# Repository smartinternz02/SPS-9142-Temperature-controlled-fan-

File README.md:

# SPS-9142-Temperature-controlled-fan-
Temperature controlled fan 

Link gor project demonstration video.
https://drive.google.com/file/d/1OC6MNtlAbGEZ7j19aoUIXOwhLdMn7zE-/view?usp=drivesdk

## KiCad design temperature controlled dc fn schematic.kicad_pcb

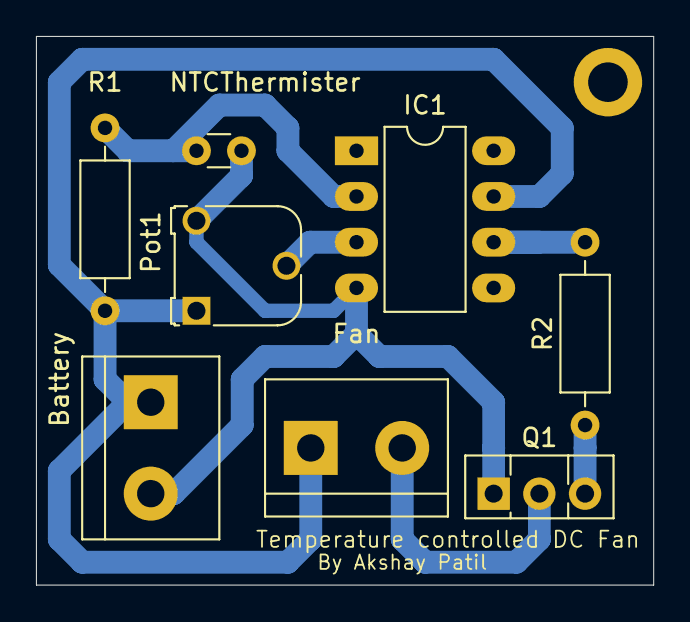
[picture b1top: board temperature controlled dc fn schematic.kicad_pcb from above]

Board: 2 copper layers, 34.3 x 30.5 mm, 8 parts (0 on the bottom side), 7 nets.

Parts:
Battery: 12 volts; TerminalBlock_bornier-2_P5.08mm
Fan: Fan; TerminalBlock_bornier-2_P5.08mm
IC1: LM741; DIP-8_W7.62mm_LongPads
NTCThermister: 10kOHM; C_Disc_D3.0mm_W1.6mm_P2.50mm
Pot1: 1Mohm; Potentiometer_Runtron_RM-065_Vertical
Q1: BD139; TO-126-3_Vertical
R1: 10Kohm; R_Axial_DIN0207_L6.3mm_D2.5mm_P10.16mm_Horizontal
R2: 4.7 Kohm; R_Axial_DIN0207_L6.3mm_D2.5mm_P10.16mm_Horizontal

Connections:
unnamed: Battery.1, Fan.1, IC1.7, Pot1.1, R1.1
unnamed: Battery.2, IC1.4, NTCThermister.2, Pot1.3, Q1.1
unnamed: IC1.2, NTCThermister.1, R1.2
unnamed: IC1.3, Pot1.2
unnamed: IC1.6, R2.2
unnamed: Fan.2, Q1.2
unnamed: Q1.3, R2.1
